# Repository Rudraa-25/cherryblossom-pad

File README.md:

# cherryblossom pad

this is my custom 12 key macropad project for the hack club hackpad. it use a seeed xiao rp2040 and got 12 switch and a small oled display. i design the case in cad and the pcb in kicad. also when [...]

here is some photos of my desgin:

**my 3d cad model:**

**my pcb layout:**

**the schematic:**

### parts u need to build this
* 1x seeed studio xiao rp2040
* 1x 0.91 oled display
* 12x mx switches 
* 12x 1n4148 diodes
* my custom pcb (in the production folder)
* my 3d printed case (also in production folder)

check out `BOOM.csv` for the full bill of materials with pricing!

### firmwere setup
i am using KMK firmwere so its super simple. u dont need to compile any uf2 file yourself.
1. download the official circuitpython uf2 for the xiao rp2040 and drag it to the board.
2. download KMK firmwere and copy the `kmk` folder to the board
3. copy my `main.py` from the firmware folder to the board.
thats it it should work now!

### credits
- made with help of github copilot to generate the BOOM.csv bill of materials

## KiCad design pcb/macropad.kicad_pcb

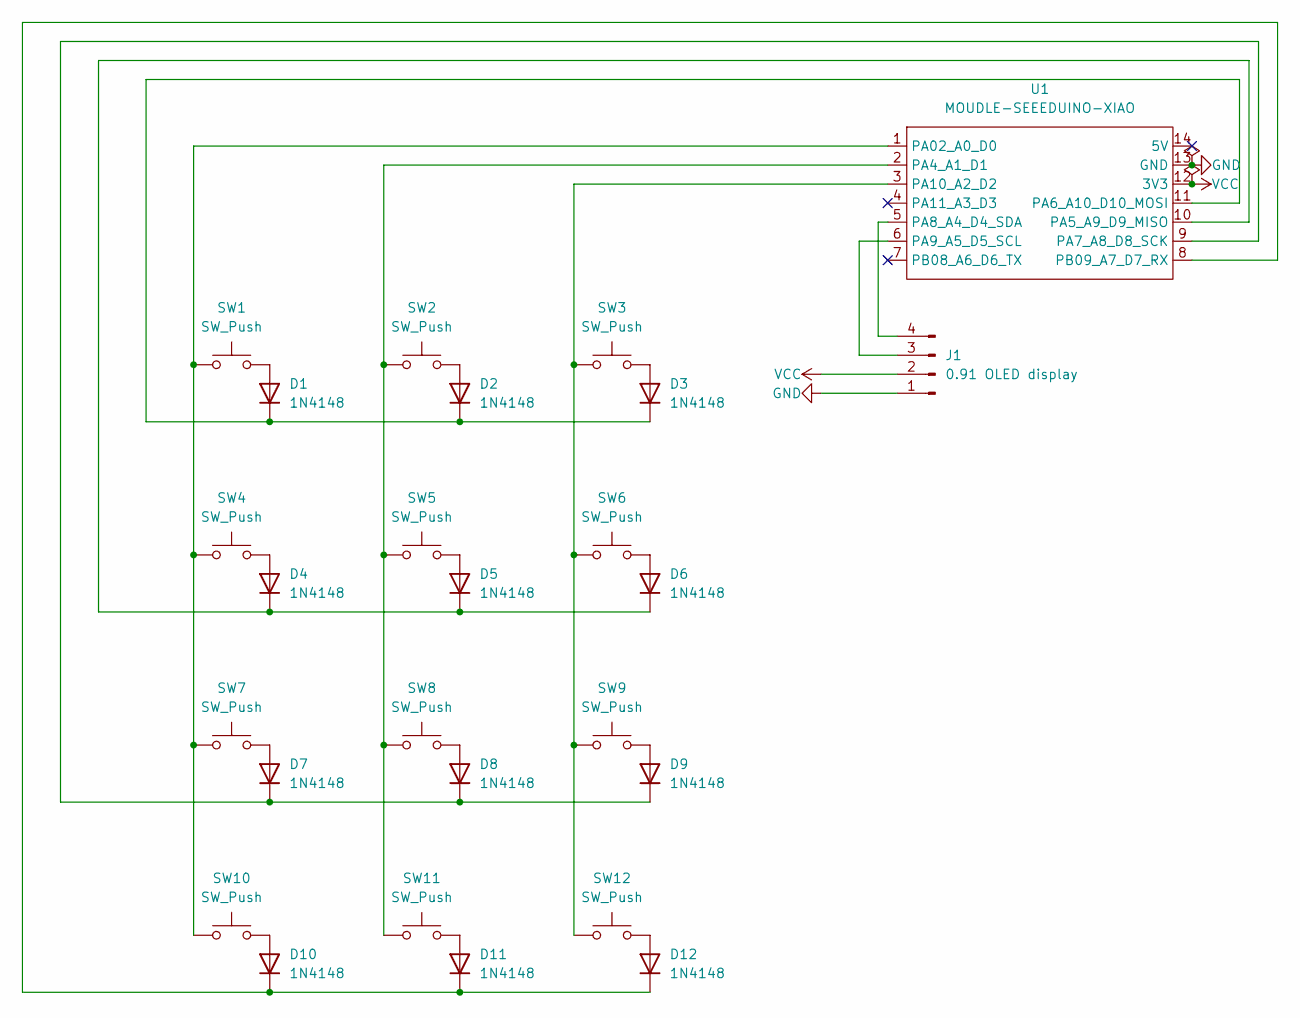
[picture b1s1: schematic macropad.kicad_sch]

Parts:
D1, D2, D3, D4, D5, D6, D7, D8, D9, D10, D11, D12: 1N4148; D_DO-35_SOD27_P7.62mm_Horizontal
J1: 0.91 OLED display; SSD1306-0.91-OLED-4pin-128x32
SW1, SW2, SW3, SW4, SW5, SW6, SW7, SW8, SW9, SW10, SW11, SW12: SW_Push; SW_Cherry_MX_1.00u_PCB
U1: MOUDLE-SEEEDUINO-XIAO; XIAO-Generic-Hybrid-14P-2.54-21X17.8MM

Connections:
GND: J1.1, U1.13 (GND)
unnamed: D1.2 (A), SW1.2
unnamed: D1.1 (K), D2.1 (K), D3.1 (K), U1.11 (PA6_A10_D10_MOSI)
unnamed: D2.2 (A), SW2.2
unnamed: D3.2 (A), SW3.2
unnamed: D4.2 (A), SW4.2
unnamed: D4.1 (K), D5.1 (K), D6.1 (K), U1.10 (PA5_A9_D9_MISO)
unnamed: D5.2 (A), SW5.2
unnamed: D6.2 (A), SW6.2
unnamed: D7.2 (A), SW7.2
unnamed: D7.1 (K), D8.1 (K), D9.1 (K), U1.9 (PA7_A8_D8_SCK)
unnamed: D8.2 (A), SW8.2
unnamed: D9.2 (A), SW9.2
unnamed: D10.2 (A), SW10.2
unnamed: D10.1 (K), D11.1 (K), D12.1 (K), U1.8 (PB09_A7_D7_RX)
unnamed: D11.2 (A), SW11.2
unnamed: D12.2 (A), SW12.2
unnamed: J1.3, U1.6 (PA9_A5_D5_SCL)
unnamed: J1.4, U1.5 (PA8_A4_D4_SDA)
unnamed: SW1.1, SW4.1, SW7.1, SW10.1, U1.1 (PA02_A0_D0)
unnamed: SW2.1, SW5.1, SW8.1, SW11.1, U1.2 (PA4_A1_D1)
unnamed: SW3.1, SW6.1, SW9.1, SW12.1, U1.3 (PA10_A2_D2)
VCC: J1.2, U1.12 (3V3)

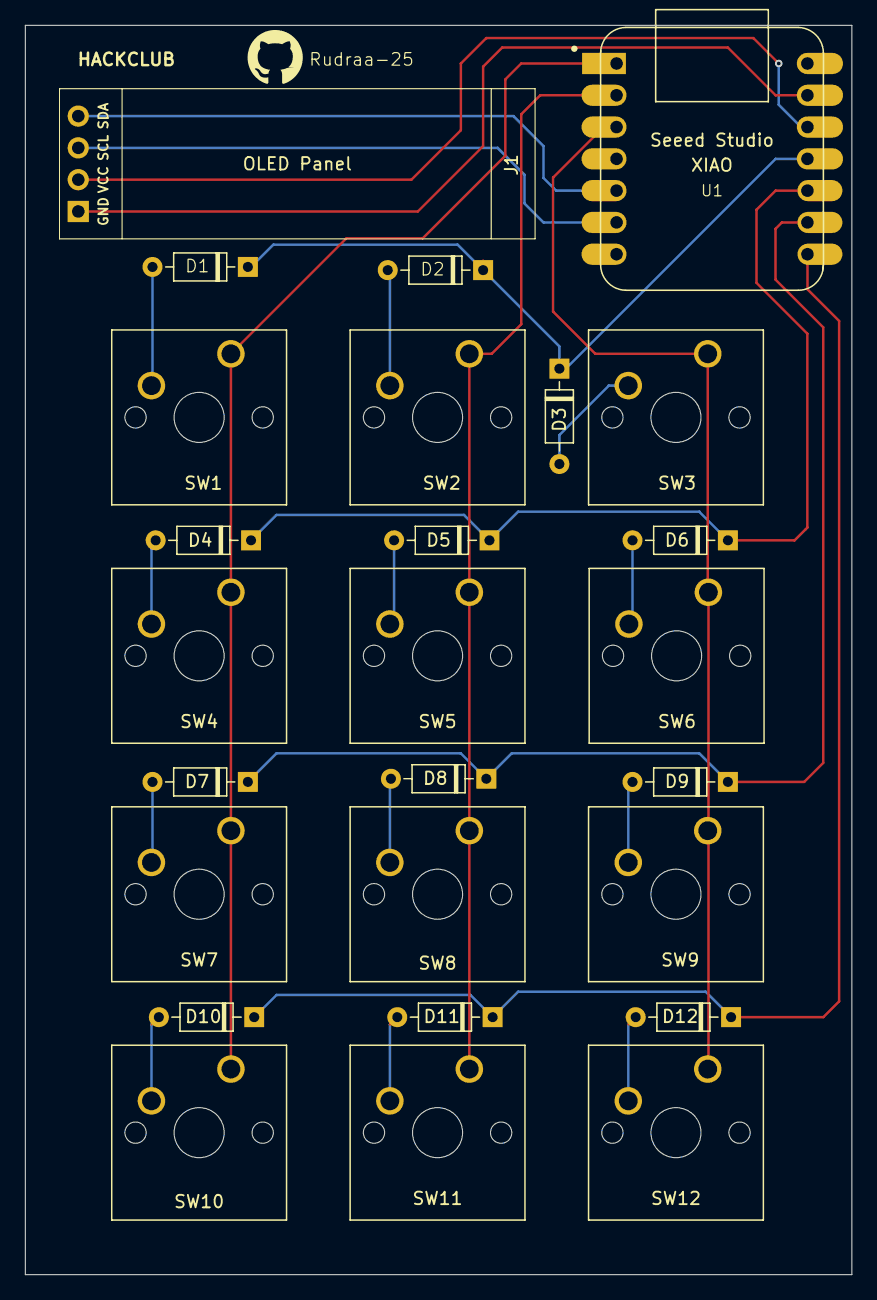
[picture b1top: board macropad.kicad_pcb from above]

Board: 2 copper layers, 66.0 x 99.8 mm, 26 parts (0 on the bottom side), 23 nets.

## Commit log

2026-06-12 Initial commit of KiCad Macropad 2.0 project and Gerbers
2026-06-16 Initial commit of cherryblossom pad for Hackpad
2026-06-29 Add bill of materials (BOOM) for macro pad project under $25
2026-06-29 Update README to credit GitHub Copilot for BOOM.csv generation
